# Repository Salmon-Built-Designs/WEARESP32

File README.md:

WearSP32 Weable ESP32 Board
===========================
Copyright 2018 Freetronics Pty Ltd  www.freetronics.com.au  

Board optimised for wearable projects.

Features:

 * ESP32 processor

More information is available at:

  http://www.freetronics.com.au/wearsp32

INSTALLATION
------------
The design is saved as an EAGLE project. EAGLE PCB design software is
available from www.cadsoftusa.com free for non-commercial use. To use
this project download it and place the directory containing these files
into the "eagle" directory on your computer. Then open EAGLE and
navigate to the project.

DISTRIBUTION
------------
The specific terms of distribution of this project are governed by the
license referenced below.

LICENSE
-------
Licensed under the TAPR Open Hardware License (www.tapr.org/OHL).
The "license" folder within this repository also contains a copy of
this license in plain text format.

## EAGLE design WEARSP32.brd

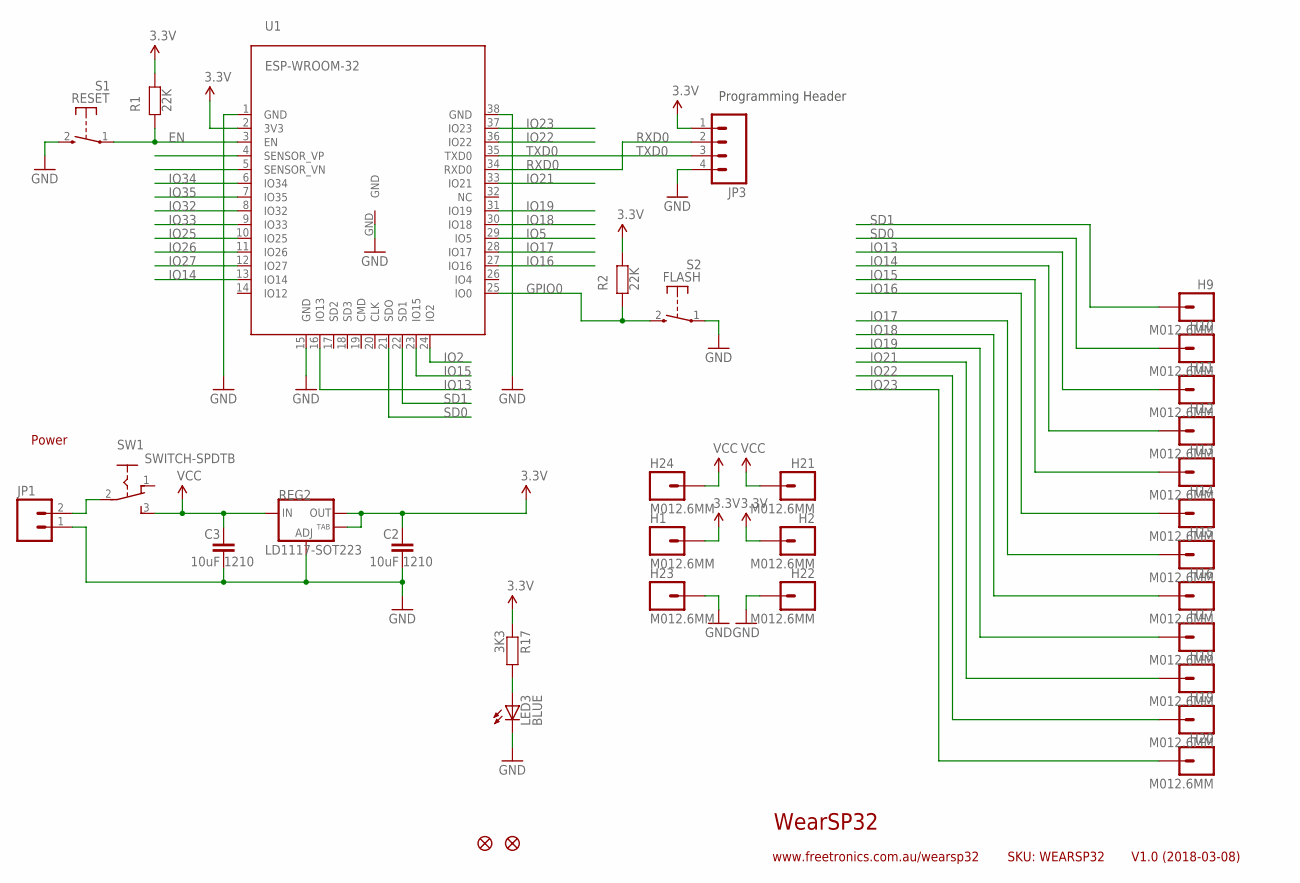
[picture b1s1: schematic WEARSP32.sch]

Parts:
C2, C3: 10uF 1210; C1210
H1, H2, H9, H10, H11, H12, H13, H14, H15, H16, H17, H18, H19, H20, H21, H22, H23, H24: M012.6MM; 1X01_2_6MM
JP1: M02JST-PTH-2; JST-2-PTH
JP3: M04PTH; 1X04
LED3: BLUE; LED-0603
R1, R2: 22K; 0603@2
R17: 3K3; 0603
REG2: LD1117-SOT223; SOT223
S1: RESET; TACTILE_SWITCH_SMD_2PIN_TINY
S2: FLASH; TACTILE_SWITCH_SMD_2PIN_TINY
SW1: SWITCH-SPDTB; SPDT-2.5MM
U1: ESP-WROOM-32
U$4, U$5: FIDUCIAL1X2.5; FIDUCIAL-1X2.5

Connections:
3.3V: C2.1, H1.1, H2.1, JP3.1, R1.1, R2.1, R17.1, REG2.2 (OUT), REG2.4 (OUT), U1.2 (3V3)
EN: R1.2, S1.1, U1.3 (EN)
GND: C2.2, C3.2, H22.1, H23.1, JP1.1, JP3.4, LED3.C, REG2.1 (ADJ), S1.2 (S), S2.1, U1.1 (GND), U1.15 (GND), U1.38 (GND), U1.GND
GPIO0: R2.2, S2.2 (S), U1.25 (IO0)
IO2: U1.24 (IO2)
IO5: U1.29 (IO5)
IO13: H11.1, U1.16 (IO13)
IO14: H12.1, U1.13 (IO14)
IO15: H13.1, U1.23 (IO15)
IO16: H14.1, U1.27 (IO16)
IO17: H15.1, U1.28 (IO17)
IO18: H16.1, U1.30 (IO18)
IO19: H17.1, U1.31 (IO19)
IO21: H18.1, U1.33 (IO21)
IO22: H19.1, U1.36 (IO22)
IO23: H20.1, U1.37 (IO23)
IO25: U1.10 (IO25)
IO26: U1.11 (IO26)
IO27: U1.12 (IO27)
IO32: U1.8 (IO32)
IO33: U1.9 (IO33)
IO34: U1.6 (IO34)
IO35: U1.7 (IO35)
unnamed: LED3.A, R17.2
unnamed: JP1.2, SW1.2
RXD0: JP3.2, U1.34 (RXD0)
SD0: H10.1, U1.21 (SDO)
SD1: H9.1, U1.22 (SD1)
TXD0: JP3.3, U1.35 (TXD0)
VCC: C3.1, H21.1, H24.1, REG2.3 (IN), SW1.3

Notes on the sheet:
WearSP32
SKU: WEARSP32
V1.0 (2018-03-08)
Power
www.freetronics.com.au/wearsp32
Programming Header

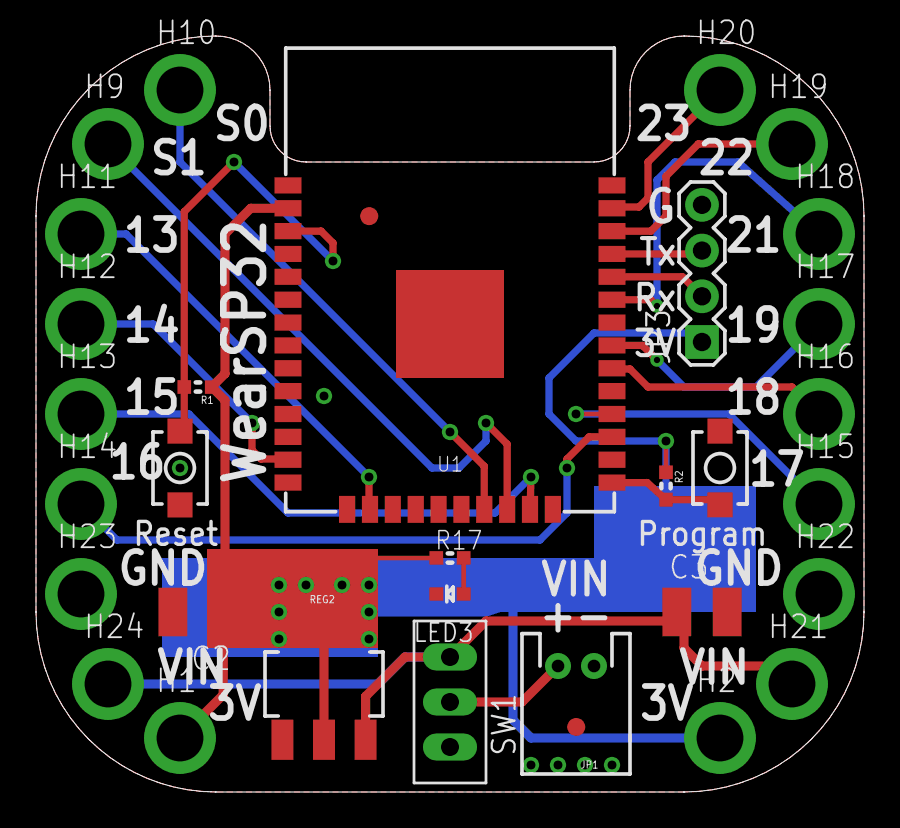
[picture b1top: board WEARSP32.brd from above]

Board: 2 copper layers, 46.0 x 42.0 mm, 33 parts (0 on the bottom side), 21 nets.

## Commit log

2018-03-08 Initial project import
2018-03-08 Added README
2018-04-25 Improved clarity of designators

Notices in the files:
WEARSP32.brd:
(C)2018 Freetronics Pty Ltd
parts and their libraries:
SparkFun-Aesthetics: Licensing: Creative Commons ShareAlike 4.0 International - https://creativecommons.org/licenses/by-sa/4.0
